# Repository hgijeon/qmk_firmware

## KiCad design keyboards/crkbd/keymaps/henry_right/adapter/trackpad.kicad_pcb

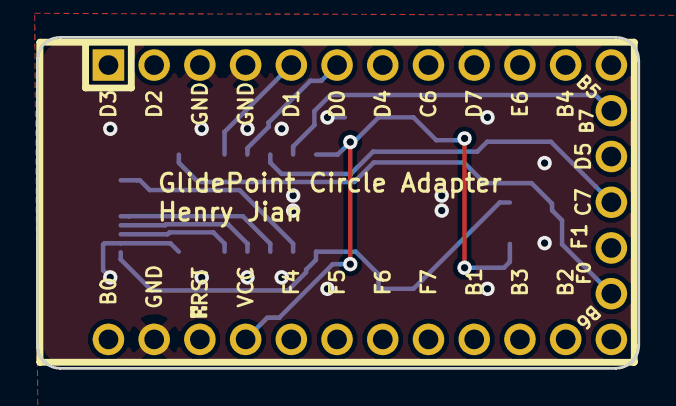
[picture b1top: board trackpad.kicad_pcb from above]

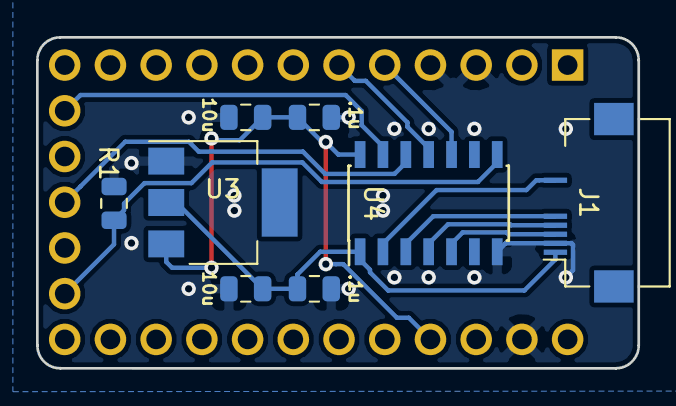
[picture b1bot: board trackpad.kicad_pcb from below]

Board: 2 copper layers, 33.4 x 18.4 mm, 9 parts (9 on the bottom side), 12 nets.

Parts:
C1, C2: 10uF; C_0805_2012Metric
C3, C4: 100nF; C_0805_2012Metric
J1: Conn_01x12; Hirose_FH12-12S-0.5SH_1x12-1MP_P0.50mm_Horizontal
R1: 3.3K; R_0805_2012Metric
U1: Elite-C; Elite-C-nf
U3: NCP1117-3.3_SOT223; SOT-223-3_TabPin2
U4: TXB0104D; SOIC-14_3.9x8.7mm_P1.27mm

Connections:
+3V3: C2.1, C3.1, J1.1, U3.2, U4.1
+5V: C1.1, C4.1, U1.21, U3.3, U4.14
GND: C1.2, C2.2, C3.2, C4.2, J1.2, R1.2, U1.3, U1.4, U1.23, U3.1, U4.7
LVL_SHIFT: R1.1, U1.29, U4.8
PD0: U1.6, U4.11
PD1: U1.5, U4.10
TP_BTN1: U1.27, U4.12
TP_BTN1_3V3: J1.5, U4.3
TP_DR: U1.25, U4.13
TP_DR_3V3: J1.9, U4.2
TP_SCL_3V3: J1.4, U4.4
TP_SDA_3V3: J1.3, U4.5

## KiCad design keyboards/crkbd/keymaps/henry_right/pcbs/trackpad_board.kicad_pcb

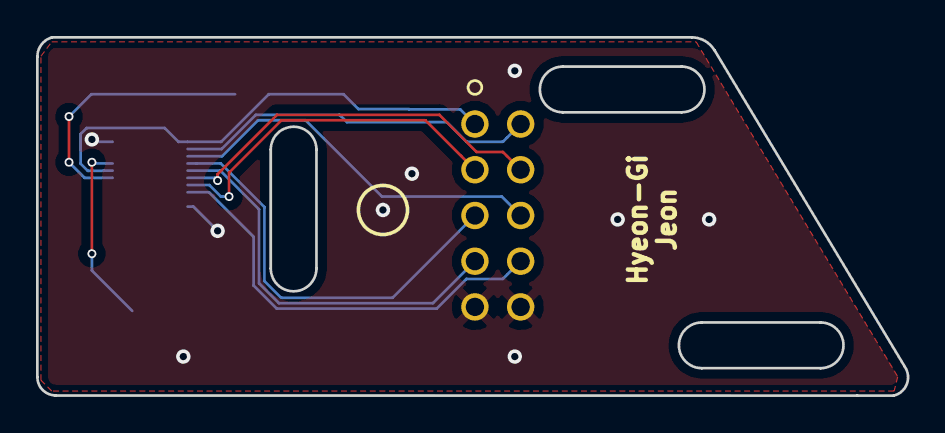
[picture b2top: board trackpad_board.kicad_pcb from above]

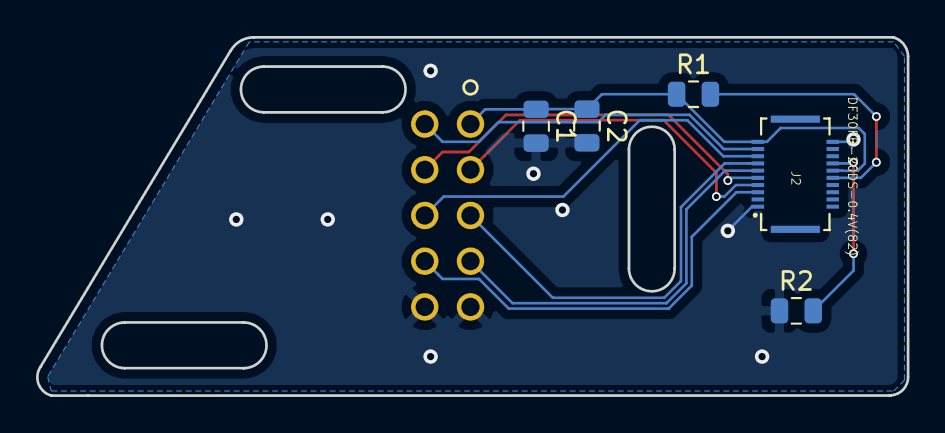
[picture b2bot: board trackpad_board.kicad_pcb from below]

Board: 2 copper layers, 48.4 x 19.9 mm, 6 parts (5 on the bottom side), 11 nets.

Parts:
C1: 100pF; C_0805_2012Metric
C2: 100nF; C_0805_2012Metric
J1: 67997-410HLF
J2: DF30FB-20DS-0.4V(82); HIROSE_DF30FB-20DS-0.4V(82)
R1, R2: 220k; R_0805_2012Metric

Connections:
+2V8: C1.1, C2.1, J1.1, J2.12, J2.19, R1.1
GND: C1.2, C2.2, J1.5, J1.10, J2.1, J2.20, R2.1
MISO_2V85: J1.8, J2.15
MOSI_2V85: J1.3, J2.13
unnamed: J2.10, R1.2
unnamed: J2.14, R2.2
SCK_2V85: J1.4, J2.11
TP_CS_2V85: J1.7, J2.9
TP_MOTION_2V85: J1.6, J2.17
TP_RESET_2v85: J1.9, J2.5
TP_SHUTDOWN_2V85: J1.2, J2.7

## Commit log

2019-06-22 레이아웃 초기 수정
2019-06-22 Lshift를 더 자주 쓸 것 같아서 더 큰 키 쪽으로 변경.
2019-06-27 오른쪽 버전 추가
2019-07-03 디바이스가 제대로 물려있을 때만 움직이도록 변경
2019-07-03 내부 스크롤 사용, 드래그 가능.
2019-07-03 trackpad수정한 pcb파일
2019-07-03 좀 더 위쪽으로 옮기고, 이름 새기기
2019-07-04 누적방식으로 변경
2019-07-04 button4 복구 및 스크롤 방향 변경
2019-07-16 xy convert
2019-07-17 트랙패드를 돌려 붙이는게 더 나음
2019-07-30 뭔가 통신은 하는듯
2019-07-30 뭔가 relative한 값을 받아오는 것 같은데 dr처리를 해야 함.
2019-07-30 dr은 안되고, 리셋처리를 했는데 잘 안됨..
2019-08-06 파일들 복사해옴
2019-08-06 컴파일은 됨
2019-08-06 뭔가 상대값은 받아오는 중
2019-08-06 안쓰게 된거 지우는 중
2019-08-06 pcb 추가
2019-08-06 배치 시작
2019-08-06 배치 거의 끝난듯
2019-08-07 drc통과
2019-08-07 실크스크린 처리
2019-08-07 경로 변경
2019-08-07 거버/드릴 파일
2019-08-27 키보드 동작은 하지만 pinnacle은 아직 안도는 상태.
2019-08-28 spi init 이후에 cs를 output으로 바꾸기 위해 순서 변경. pd2 serial 임시로 비활성화
2019-09-02 동작하는 코드
2019-09-03 방향 맞추기 및 날리는 간격 조정
2019-09-03 방향 맞추기 및 날리는 간격 조정2
2019-09-03 설정변경
2019-09-29 i2c로 변경중
2019-09-29 최소구성요소
2019-10-01 아트웍 시작 전.
2019-10-01 배치 변경
2019-10-01 트랙 제거
2019-10-01 안쓰는 패드 빼기
2019-10-01 seeed studio 에 주문한 파일
2019-10-22 핀들이 안나오도록 다시 처리
2020-01-23 어댑터 없이 기본설정 사용.

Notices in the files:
parts and their libraries:
Copyright 2016 Accelerated Designs. All rights reserved.
